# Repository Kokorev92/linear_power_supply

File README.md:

# Проект регулируемого линейного источника питания

Регулируемый линейный источник питания на базе микросхемы LM338. Поддерживает выходной ток до 5А.

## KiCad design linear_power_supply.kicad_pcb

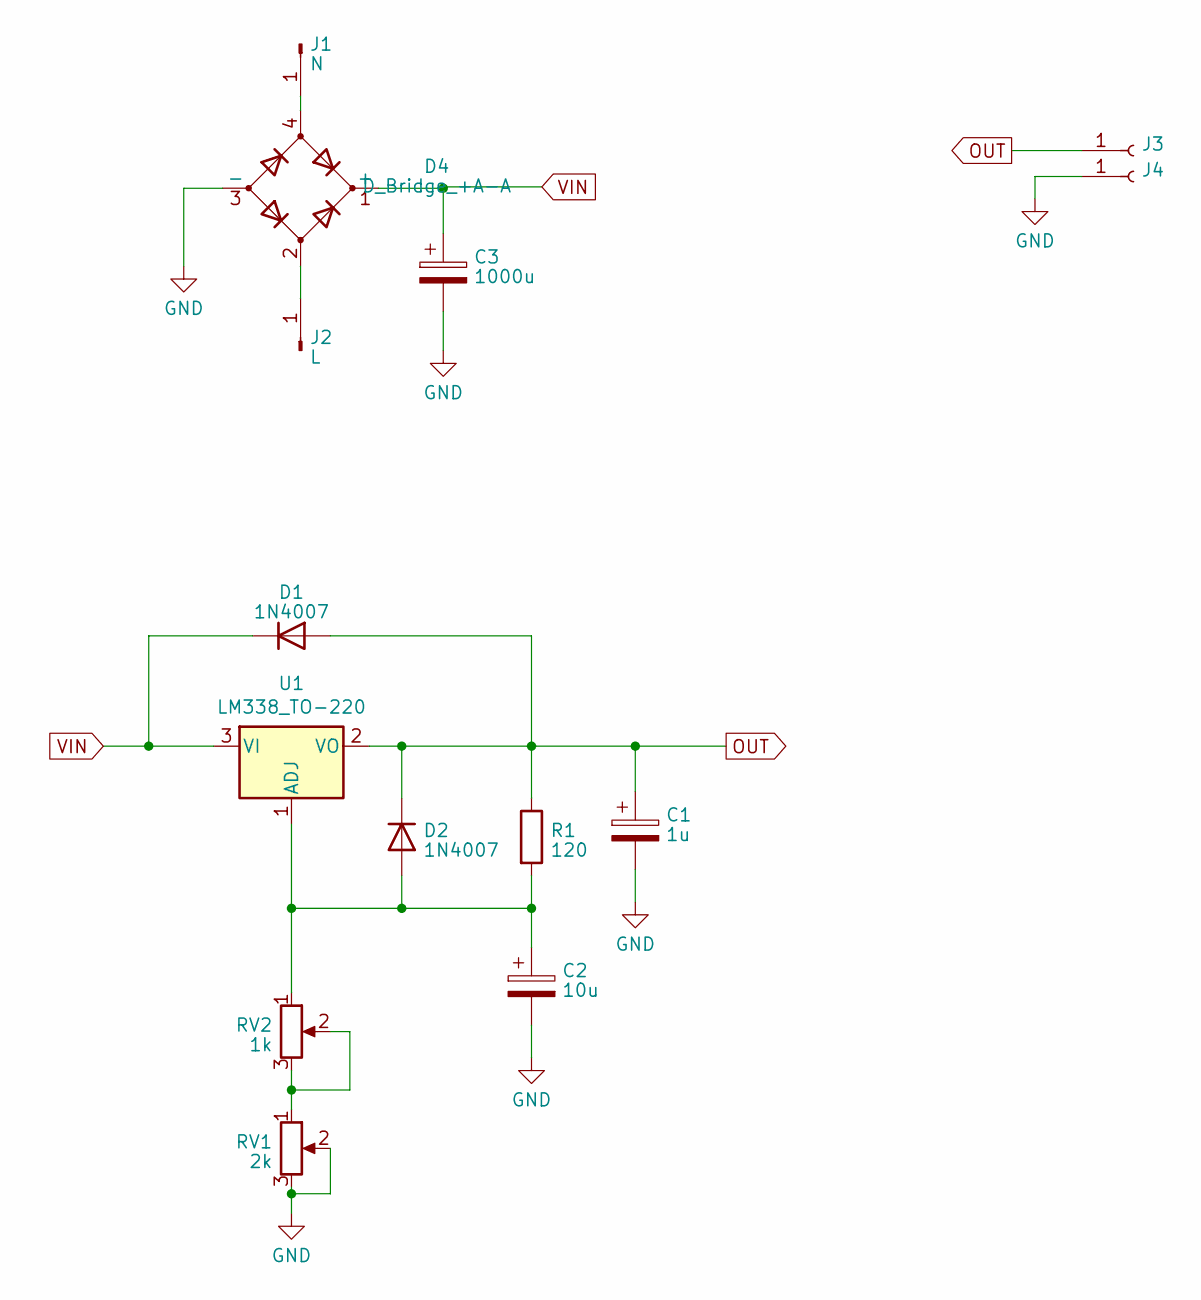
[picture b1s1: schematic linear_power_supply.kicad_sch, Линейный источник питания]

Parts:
C1: 1u; CP_Radial_D10.0mm_P5.00mm
C2: 10u; CP_Radial_D10.0mm_P5.00mm
C3: 1000u; CP_Radial_D8.0mm_P5.00mm
D1, D2: 1N4007; D_DO-41_SOD81_P10.16mm_Horizontal
D4: D_Bridge_+A-A; Diode_Bridge_19.0x19.0x6.8mm_P12.7mm
J1: N; MountingHole_3.5mm_Pad
J2: L; MountingHole_3.5mm_Pad
J3, J4: MountingHole_3.5mm_Pad
R1: 120; R_Axial_DIN0411_L9.9mm_D3.6mm_P20.32mm_Horizontal
RV1: 2k; PinSocket_1x03_P2.54mm_Vertical
RV2: 1k; PinSocket_1x03_P2.54mm_Vertical
U1: LM338_TO-220; TO-220-3_Vertical

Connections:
GND: C1.2, C2.2, C3.2, D4.3 (-), J4.1, RV1.2, RV1.3
unnamed: C2.1, D2.2 (A), R1.2, RV2.1, U1.1 (ADJ)
unnamed: D4.4, J1.1
unnamed: D4.2, J2.1
unnamed: RV1.1, RV2.2, RV2.3
OUT: C1.1, D1.2 (A), D2.1 (K), J3.1, R1.1, U1.2 (VO)
VIN: C3.1, D1.1 (K), D4.1 (+), U1.3 (VI)

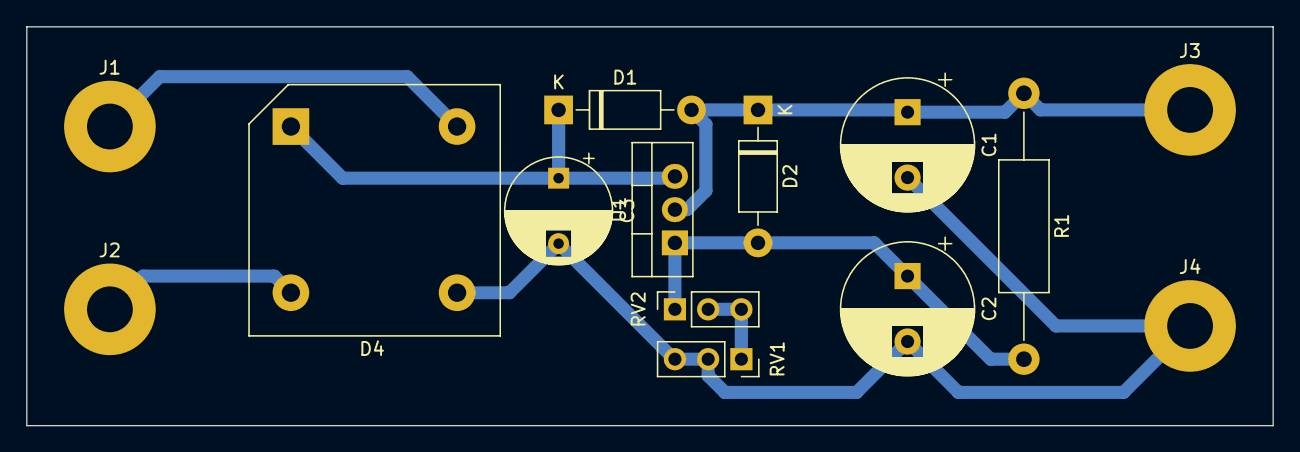
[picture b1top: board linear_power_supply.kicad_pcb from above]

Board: 2 copper layers, 95.2 x 30.5 mm, 14 parts (0 on the bottom side), 7 nets.

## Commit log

2022-03-11 add readme
2023-02-26 [wip]: cknverted to kicad 7 version and changes scheme and PCB
2023-02-27 [wip]: заливка GND зоны
